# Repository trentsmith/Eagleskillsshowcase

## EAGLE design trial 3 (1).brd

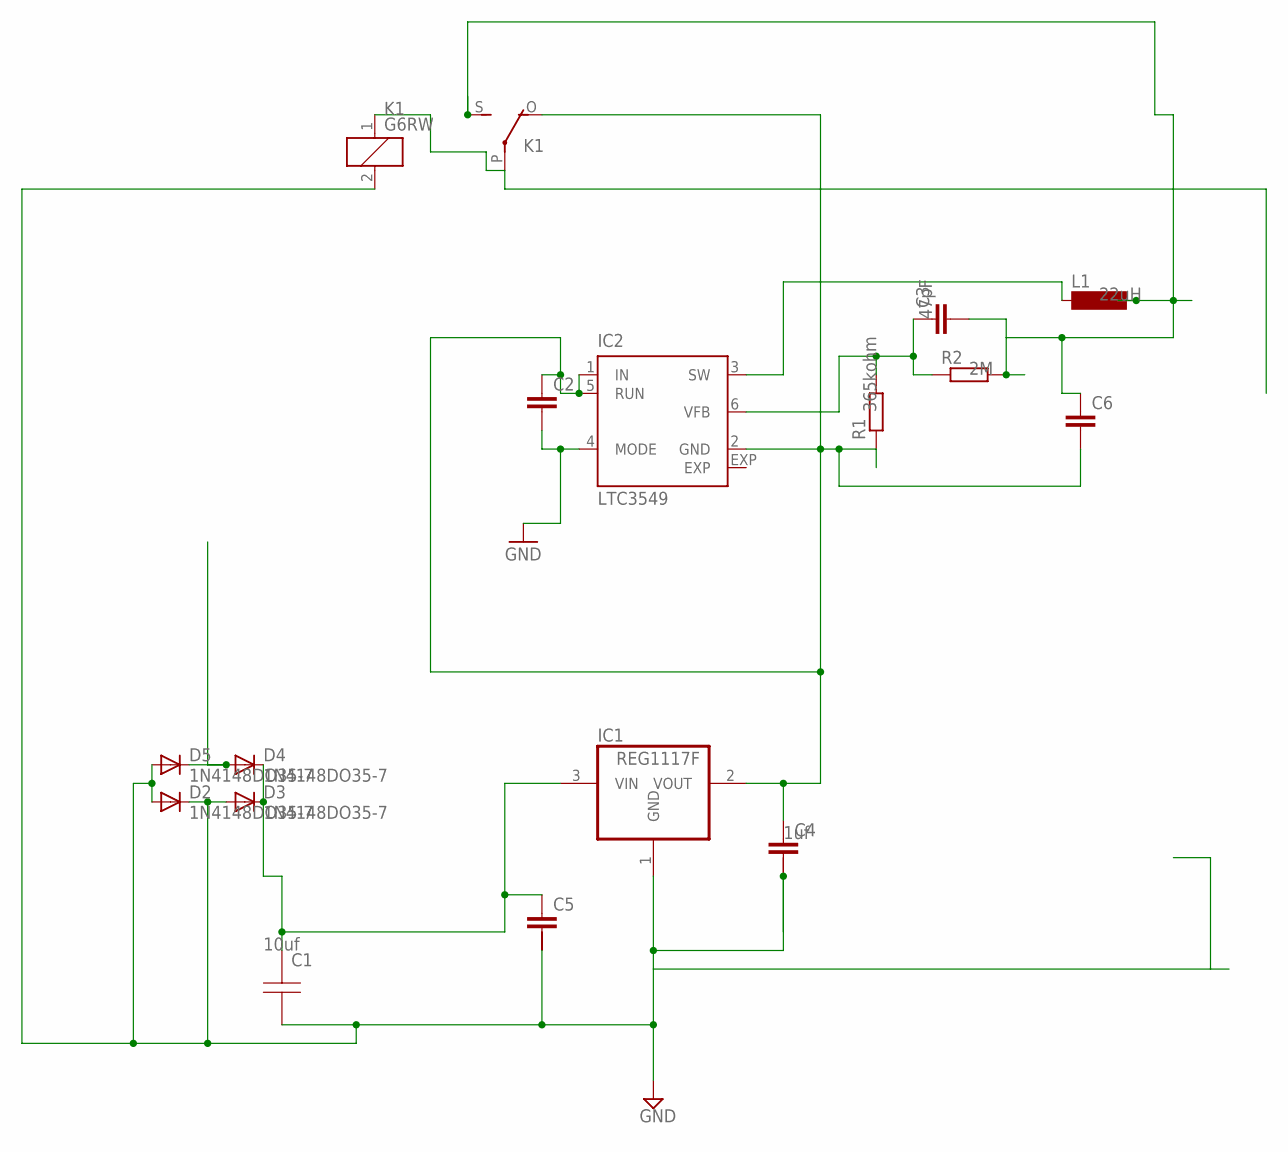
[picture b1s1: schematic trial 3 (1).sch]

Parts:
C1: CAP; C0805
C2: C2,5-3; C2.5-3
C3, C6: C2.5/4; C2.5-4
C4, C5: C-2.5-5/5; C2.5/5-5
D2, D3, D4, D5: 1N4148DO35-7; DO35-7
IC1: REG1117F; DD-3
IC2: LTC3549; DFN6-2X3
K1: G6RW
L1: MS85
R1, R2: R0207/10; 0207/10

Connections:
GND: C1.2 (B), C2.2, C4.2, C5.2, D2.A, D2.C, D3.A, D5.A, IC1.1 (GND), IC2.4 (MODE), K1.2
unnamed: C1.1 (A), C5.1, D3.C, D4.C, IC1.3 (VIN)
unnamed: C2.1, C4.1, C6.2, IC1.2 (VOUT), IC2.1 (IN), IC2.2 (GND), IC2.5 (RUN), K1.O
unnamed: C3.2, C6.1, K1.S, L1.2, R2.2
unnamed: D4.A, D5.C
unnamed: C3.1, IC2.6 (VFB), R1.2, R2.1
unnamed: IC2.3 (SW), L1.1

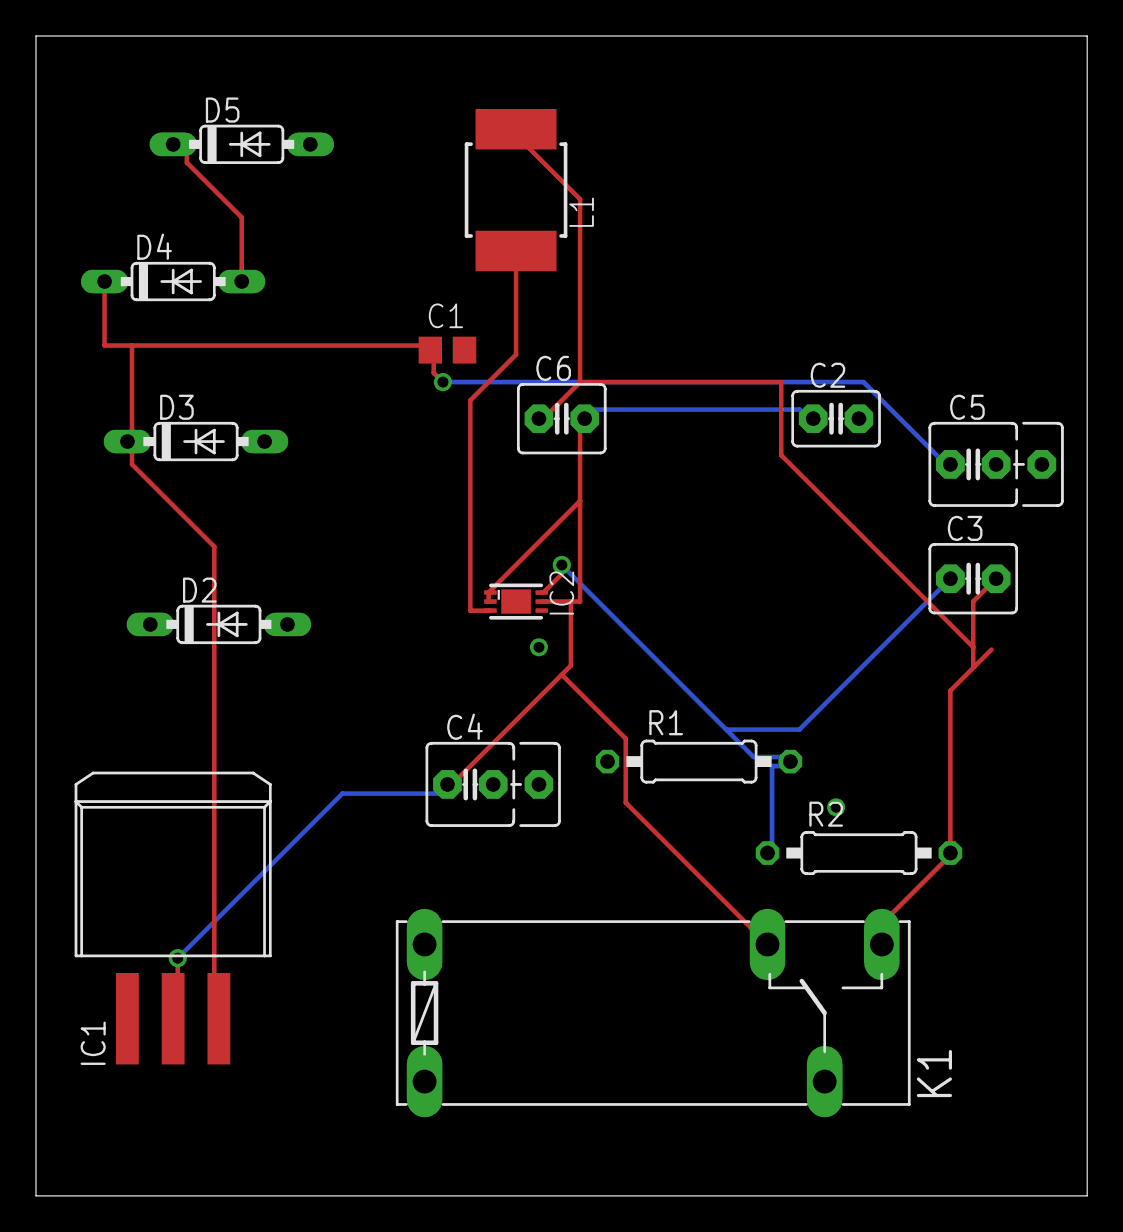
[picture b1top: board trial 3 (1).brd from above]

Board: 2 copper layers, 58.4 x 64.4 mm, 16 parts (0 on the bottom side), 7 nets.
